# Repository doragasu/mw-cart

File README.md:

# WARNING: THIS PROJECT HAS MOVED

You can find the most recent version at the [mw-cart GitLab project page](https://gitlab.com/doragasu/mw-cart). This repository will be kept as is, and will not be updated anymore.

# mw-cart
MegaWiFi Cartridge

This cartridge is for the MegaWiFi project. It consists of a cartridge for the SEGA Genesis/Megadrive console, along with a WiFi interface, allowing brave programmers to implement games with online gaming, leaderboards, evil DLCs, etc.

This project was initially created for 1985alternativo, but to this day, no brave soul has dared to make an online game using this cart. Will you give it a try?

Have a look to the [github project page](https://github.com/doragasu/mw) for more information.

## License
mw-cart is licensed under the [CERN OHL 1.2](http://www.ohwr.org/licenses/cern-ohl/v1.2) license. You are free to study, distribute and make modifications to the Documentation, under the aforementioned license terms. You are also free to make cartridges derived from the Documentation for non-commercial purposes. If you want to make a commercial Product using this Documentation, please contact me to obtain a licence.

## About CAD files
Electronic CAD design files are for KiCAD Open Source electronics design suite. Please install latest version along with KiCAD libraries to open the project. When opening schematic, KiCAD will most likely complain about missing library "doragasu". Despite this warning, the schematic should load nicely (using the cached libraries). To avoid this message, install [the missing library](https://github.com/doragasu/doragasu-kicad-lib) and make sure to configure it in the schematic editor.

The files under `gerber` directory are for PCB fabrication. Send them to your favorite PCB fab house.

Enjoy!

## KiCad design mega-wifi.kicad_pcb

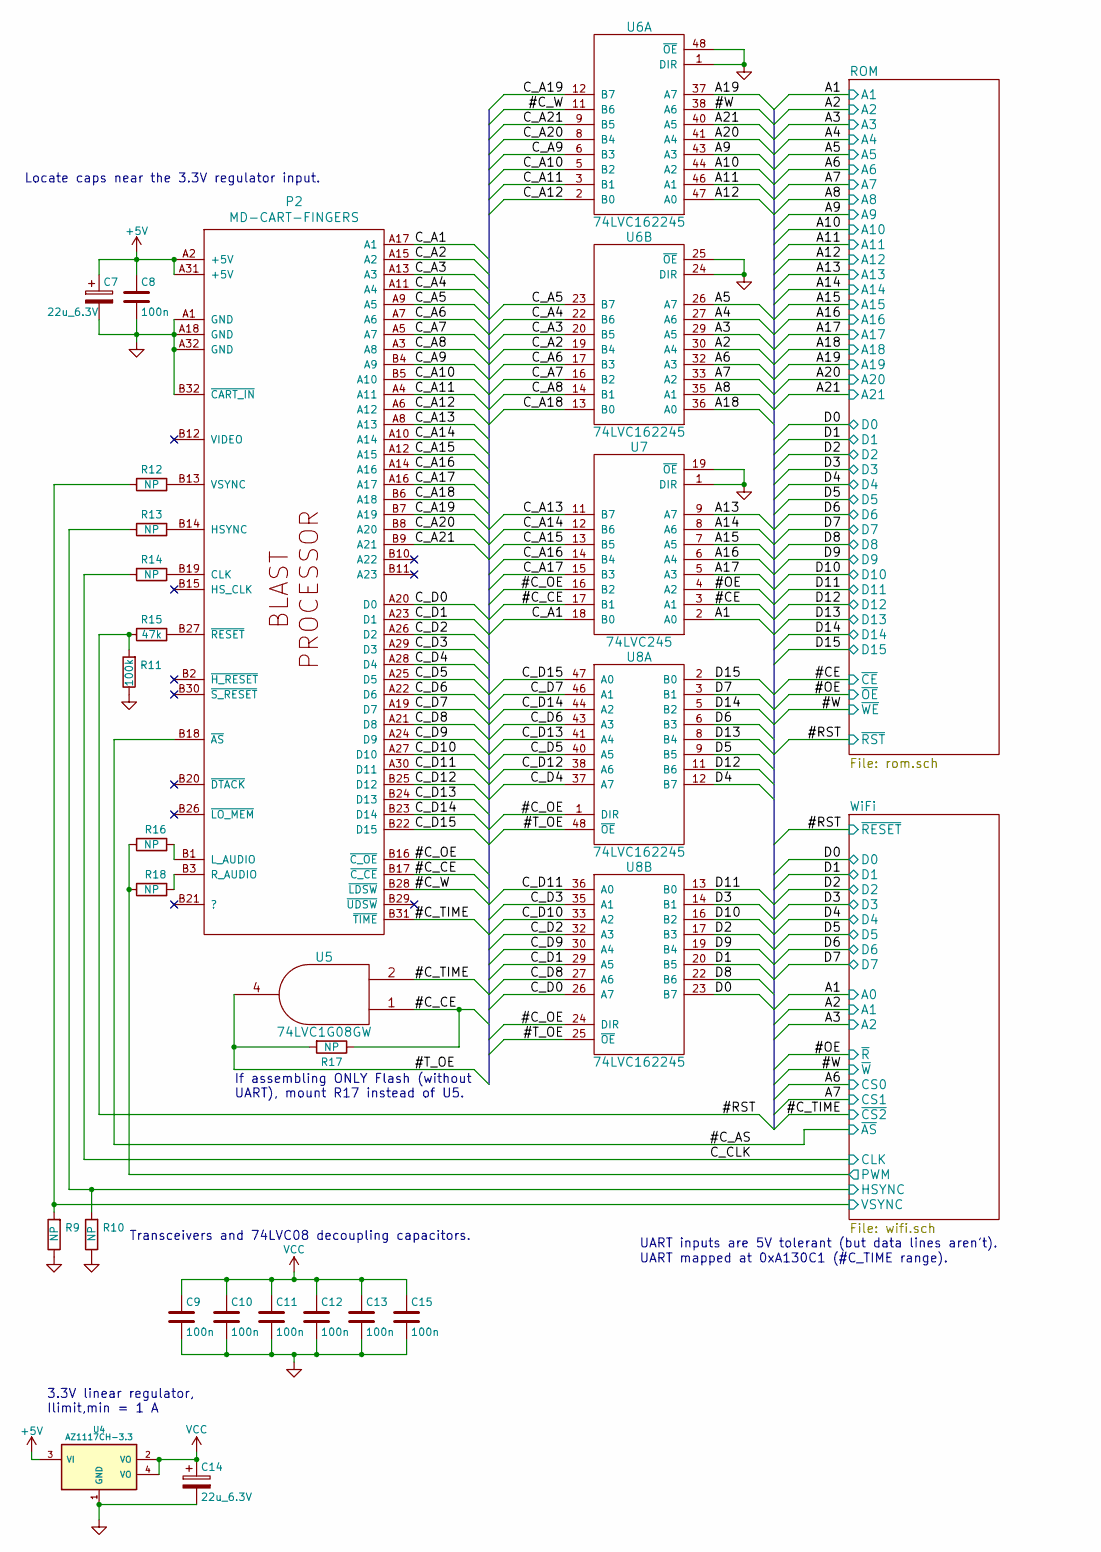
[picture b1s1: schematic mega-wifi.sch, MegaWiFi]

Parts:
C7, C14: 22u_6.3V; c_elec_4x4.5; LCSC# C250865
C8, C9, C10, C11, C12, C13, C15: 100n; C_0805; LCSC# C2830722
P2: MD-CART-FINGERS
R9, R10, R12, R13: NP; R_0805
R11: 100k; R_0805; LCSC# C237121
R14, R16, R17, R18: NP; JUMPER_0805
R15: 47k; R_0805; LCSC# C144558
U4: AZ1117CH-3.3; SOT-223; LCSC# C351784
U5: 74LVC1G08GW; SOT23-5; LCSC# C434068
U6, U8: 74LVC162245; TSSOP-48_6.1x12.5mm_Pitch0.5mm; LCSC# C6069
U7: 74LVC245; SSOP-20_4.4x6.5mm_Pitch0.65mm; LCSC# C393617

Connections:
+5V: C7.1, C8.1, P2.A2 (+5V), P2.A31 (+5V), U4.3 (VI)
/#CE: U7.3 (A1); also elsewhere on the board
/#C_AS: P2.B18 (~AS); also elsewhere on the board
/#C_CE: P2.B17 (~C_CE), R17.1, U5.1 (B), U7.17 (B1)
/#C_OE: P2.B16 (~C_OE), U7.16 (B2), U8.1 (DIR), U8.24 (DIR)
/#C_TIME: P2.B31 (~TIME), U5.2 (A); also elsewhere on the board
/#C_W: P2.B28 (~LDSW), U6.11 (B6)
/#OE: U7.4 (A2); also elsewhere on the board
/#RST: R11.2, R15.1; also elsewhere on the board
/#T_OE: R17.2, U5.4 (Y), U8.25 (~OE), U8.48 (~OE)
/#W: U6.38 (A6); also elsewhere on the board
/A1: U7.2 (A0); also elsewhere on the board
/A2: U6.30 (A4); also elsewhere on the board
/A3: U6.29 (A5); also elsewhere on the board
/A4: U6.27 (A6); also elsewhere on the board
/A5: U6.26 (A7); also elsewhere on the board
/A6: U6.32 (A3); also elsewhere on the board
/A7: U6.33 (A2); also elsewhere on the board
/A8: U6.35 (A1); also elsewhere on the board
/A9: U6.43 (A3); also elsewhere on the board
/A10: U6.44 (A2); also elsewhere on the board
/A11: U6.46 (A1); also elsewhere on the board
/A12: U6.47 (A0); also elsewhere on the board
/A13: U7.9 (A7); also elsewhere on the board
/A14: U7.8 (A6); also elsewhere on the board
/A15: U7.7 (A5); also elsewhere on the board
/A16: U7.6 (A4); also elsewhere on the board
/A17: U7.5 (A3); also elsewhere on the board
/A18: U6.36 (A0); also elsewhere on the board
/A19: U6.37 (A7); also elsewhere on the board
/A20: U6.41 (A4); also elsewhere on the board
/A21: U6.40 (A5); also elsewhere on the board
/C_A1: P2.A17 (A1), U7.18 (B0)
/C_A2: P2.A15 (A2), U6.19 (B4)
/C_A3: P2.A13 (A3), U6.20 (B5)
/C_A4: P2.A11 (A4), U6.22 (B6)
/C_A5: P2.A9 (A5), U6.23 (B7)
/C_A6: P2.A7 (A6), U6.17 (B3)
/C_A7: P2.A5 (A7), U6.16 (B2)
/C_A8: P2.A3 (A8), U6.14 (B1)
/C_A9: P2.B4 (A9), U6.6 (B3)
/C_A10: P2.B5 (A10), U6.5 (B2)
/C_A11: P2.A4 (A11), U6.3 (B1)
/C_A12: P2.A6 (A12), U6.2 (B0)
/C_A13: P2.A8 (A13), U7.11 (B7)
/C_A14: P2.A10 (A14), U7.12 (B6)
/C_A15: P2.A12 (A15), U7.13 (B5)
/C_A16: P2.A14 (A16), U7.14 (B4)
/C_A17: P2.A16 (A17), U7.15 (B3)
/C_A18: P2.B6 (A18), U6.13 (B0)
/C_A19: P2.B7 (A19), U6.12 (B7)
/C_A20: P2.B8 (A20), U6.8 (B4)
/C_A21: P2.B9 (A21), U6.9 (B5)
/C_CLK: R14.2; also elsewhere on the board
/C_D0: P2.A20 (D0), U8.26 (A7)
/C_D1: P2.A23 (D1), U8.29 (A5)
/C_D2: P2.A26 (D2), U8.32 (A3)
/C_D3: P2.A29 (D3), U8.35 (A1)
/C_D4: P2.A28 (D4), U8.37 (A7)
/C_D5: P2.A25 (D5), U8.40 (A5)
/C_D6: P2.A22 (D6), U8.43 (A3)
/C_D7: P2.A19 (D7), U8.46 (A1)
/C_D8: P2.A21 (D8), U8.27 (A6)
/C_D9: P2.A24 (D9), U8.30 (A4)
/C_D10: P2.A27 (D10), U8.33 (A2)
/C_D11: P2.A30 (D11), U8.36 (A0)
/C_D12: P2.B25 (D12), U8.38 (A6)
/C_D13: P2.B24 (D13), U8.41 (A4)
/C_D14: P2.B23 (D14), U8.44 (A2)
/C_D15: P2.B22 (D15), U8.47 (A0)
/D0: U8.23 (B7); also elsewhere on the board
/D1: U8.20 (B5); also elsewhere on the board
/D2: U8.17 (B3); also elsewhere on the board
/D3: U8.14 (B1); also elsewhere on the board
/D4: U8.12 (B7); also elsewhere on the board
/D5: U8.9 (B5); also elsewhere on the board
/D6: U8.6 (B3); also elsewhere on the board
/D7: U8.3 (B1); also elsewhere on the board
/D8: U8.22 (B6); also elsewhere on the board
/D9: U8.19 (B4); also elsewhere on the board
/D10: U8.16 (B2); also elsewhere on the board
/D11: U8.13 (B0); also elsewhere on the board
/D12: U8.11 (B6); also elsewhere on the board
/D13: U8.8 (B4); also elsewhere on the board
/D14: U8.5 (B2); also elsewhere on the board
/D15: U8.2 (B0); also elsewhere on the board
/WiFi/HSYNC: R10.2, R13.1; also elsewhere on the board
/WiFi/PWM: R16.1, R18.1; also elsewhere on the board
/WiFi/VSYNC: R9.2, R12.1; also elsewhere on the board
GND: C7.2, C8.2, C9.2, C10.2, C11.2, C12.2, C13.2, C14.2, C15.2, P2.A1 (GND), P2.A18 (GND), P2.A32 (GND), P2.B32 (~CART_IN), R9.1, R10.1, R11.1, U4.1 (GND), U5.3 (GND), U6.1 (DIR), U6.4 (GND), U6.10 (GND), U6.15 (GND), U6.21 (GND), U6.24 (DIR), U6.25 (~OE), U6.28 (GND), U6.34 (GND), U6.39 (GND), U6.45 (GND), U6.48 (~OE), U7.1 (DIR), U7.10 (GND), U7.19 (~OE), U8.4 (GND), U8.10 (GND), U8.15 (GND), U8.21 (GND), U8.28 (GND), U8.34 (GND), U8.39 (GND), U8.45 (GND); also elsewhere on the board
unnamed: P2.B1 (L_AUDIO), R16.2
unnamed: P2.B3 (R_AUDIO), R18.2
unnamed: P2.B13 (VSYNC), R12.2
unnamed: P2.B14 (HSYNC), R13.2
unnamed: P2.B19 (CLK), R14.1
unnamed: P2.B27 (~RESET), R15.2
VCC: C9.1, C10.1, C11.1, C12.1, C13.1, C14.1, C15.1, U4.2 (VO), U4.4 (VO), U5.5 (VCC), U6.7 (VCC), U6.18 (VCC), U6.31 (VCC), U6.42 (VCC), U7.20 (VCC), U8.7 (VCC), U8.18 (VCC), U8.31 (VCC), U8.42 (VCC); also elsewhere on the board

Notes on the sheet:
UART inputs are 5V tolerant (but data lines aren't).
3.3V linear regulator, Ilimit,min = 1 A
UART mapped at 0xA130C1 (#C_TIME range).
Locate caps near the 3.3V regulator input.
Transceivers and 74LVC08 decoupling capacitors.
If assembling ONLY Flash (without UART), mount R17 instead of U5.

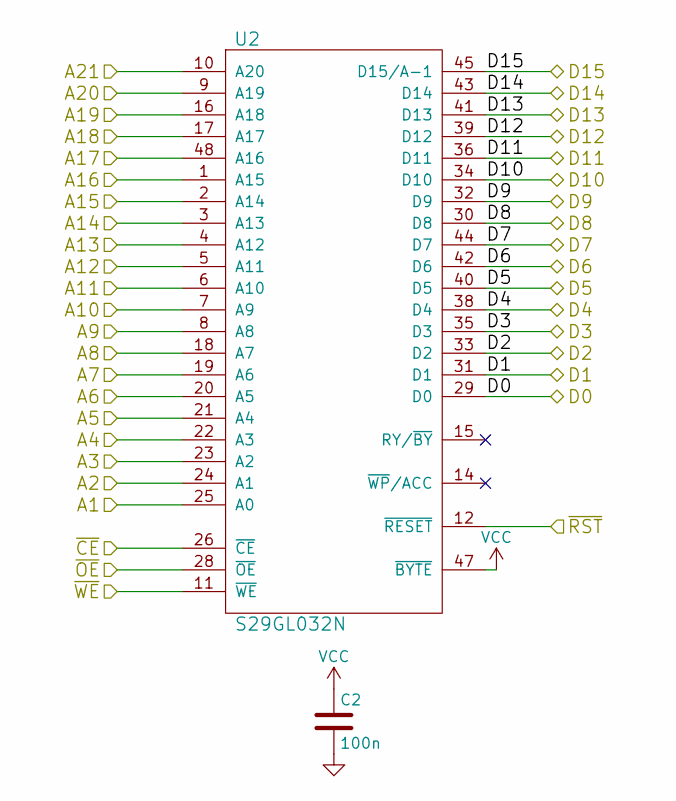
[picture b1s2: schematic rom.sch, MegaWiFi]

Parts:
C2: 100n; C_0805; LCSC# C2830722
U2: S29GL032N; TSOP48SP; LCSC# C62389

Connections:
/#CE: U2.26 (~CE); also elsewhere on the board
/#OE: U2.28 (~OE); also elsewhere on the board
/#RST: U2.12 (~RESET); also elsewhere on the board
/#W: U2.11 (~WE); also elsewhere on the board
/A1: U2.25 (A0); also elsewhere on the board
/A2: U2.24 (A1); also elsewhere on the board
/A3: U2.23 (A2); also elsewhere on the board
/A4: U2.22 (A3); also elsewhere on the board
/A5: U2.21 (A4); also elsewhere on the board
/A6: U2.20 (A5); also elsewhere on the board
/A7: U2.19 (A6); also elsewhere on the board
/A8: U2.18 (A7); also elsewhere on the board
/A9: U2.8 (A8); also elsewhere on the board
/A10: U2.7 (A9); also elsewhere on the board
/A11: U2.6 (A10); also elsewhere on the board
/A12: U2.5 (A11); also elsewhere on the board
/A13: U2.4 (A12); also elsewhere on the board
/A14: U2.3 (A13); also elsewhere on the board
/A15: U2.2 (A14); also elsewhere on the board
/A16: U2.1 (A15); also elsewhere on the board
/A17: U2.48 (A16); also elsewhere on the board
/A18: U2.17 (A17); also elsewhere on the board
/A19: U2.16 (A18); also elsewhere on the board
/A20: U2.9 (A19); also elsewhere on the board
/A21: U2.10 (A20); also elsewhere on the board
/D0: U2.29 (D0); also elsewhere on the board
/D1: U2.31 (D1); also elsewhere on the board
/D2: U2.33 (D2); also elsewhere on the board
/D3: U2.35 (D3); also elsewhere on the board
/D4: U2.38 (D4); also elsewhere on the board
/D5: U2.40 (D5); also elsewhere on the board
/D6: U2.42 (D6); also elsewhere on the board
/D7: U2.44 (D7); also elsewhere on the board
/D8: U2.30 (D8); also elsewhere on the board
/D9: U2.32 (D9); also elsewhere on the board
/D10: U2.34 (D10); also elsewhere on the board
/D11: U2.36 (D11); also elsewhere on the board
/D12: U2.39 (D12); also elsewhere on the board
/D13: U2.41 (D13); also elsewhere on the board
/D14: U2.43 (D14); also elsewhere on the board
/D15: U2.45 (D15/A-1); also elsewhere on the board
GND: C2.2, U2.27 (GND), U2.46 (GND); also elsewhere on the board
VCC: C2.1, U2.37 (VCC), U2.47 (~BYTE); also elsewhere on the board

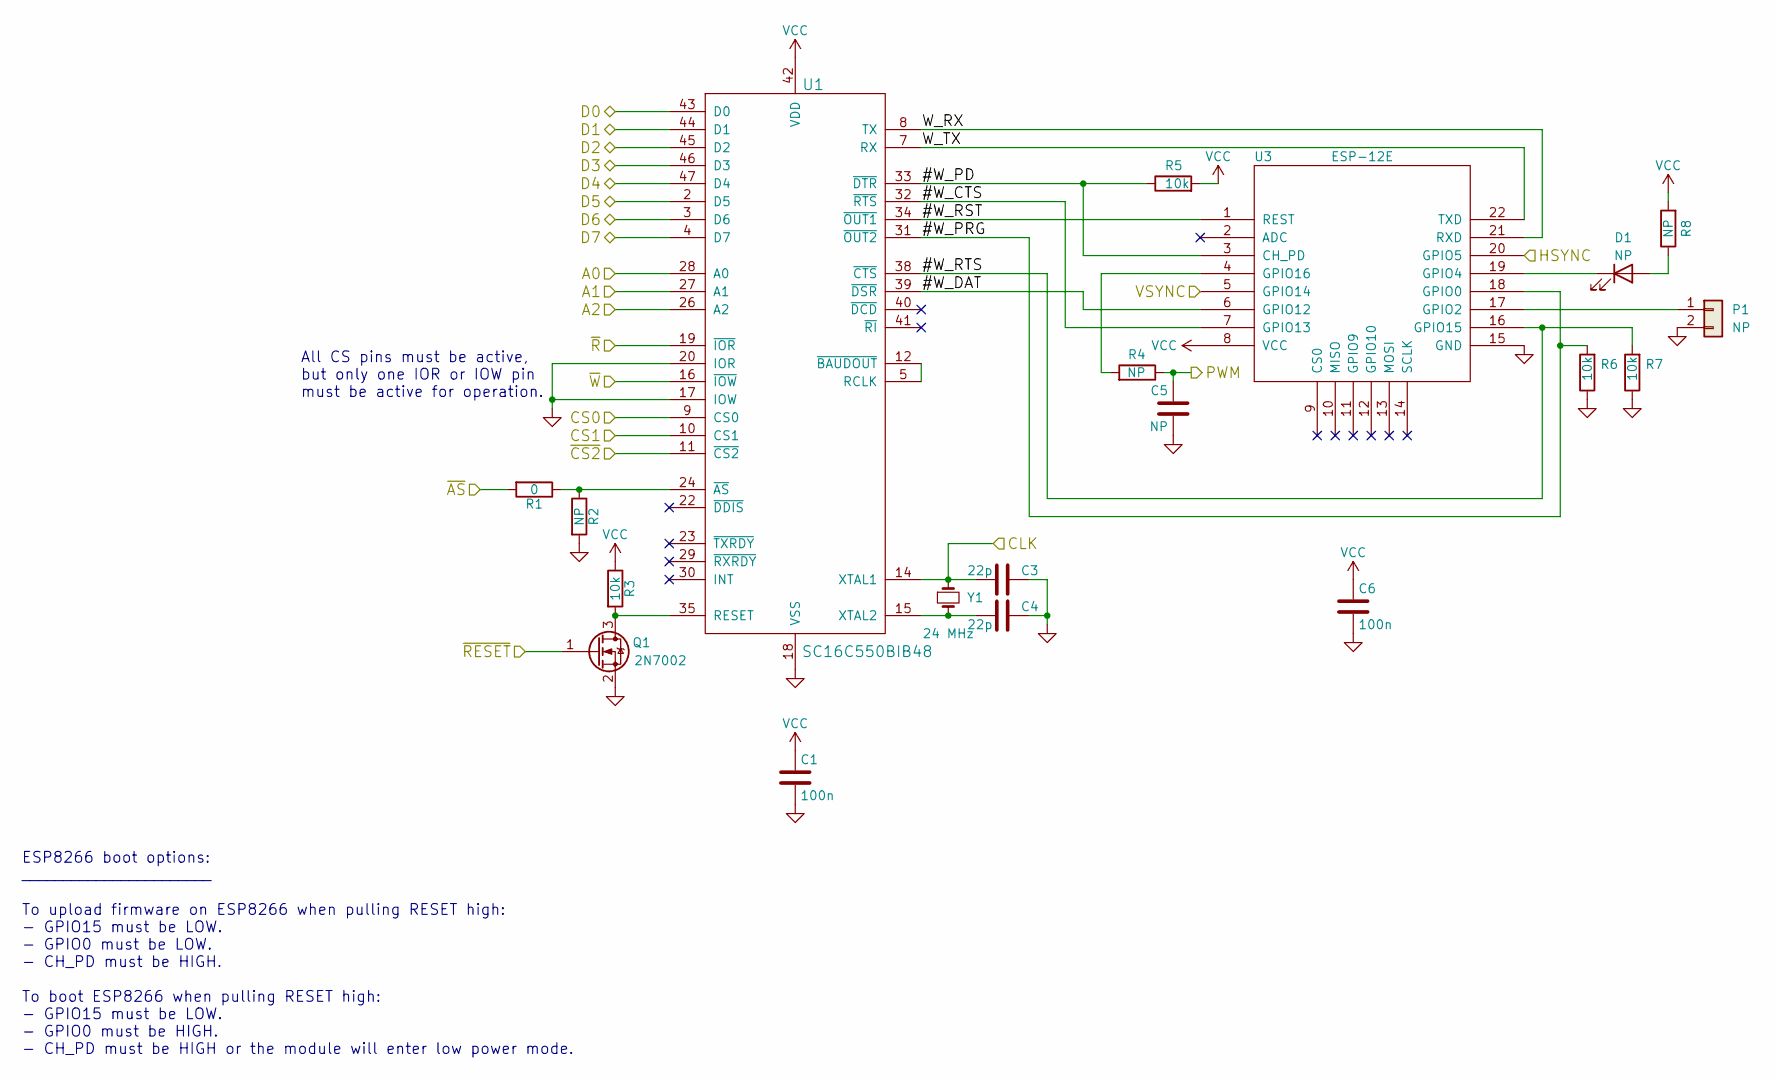
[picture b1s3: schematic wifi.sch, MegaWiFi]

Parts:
C1, C6: 100n; C_0805; LCSC# C2830722
C3, C4: 22p; C_0805; LCSC# C237185
C5: NP; C_0805; LCSC# C2830722
D1: NP; LED-0603
P1: NP; PinHeader_1x02_P2.54mm_Vertical
Q1: 2N7002; sot23; LCSC# C306856
R1: 0; JUMPER_0805; LCSC# C96345
R2, R4, R8: NP; R_0805
R3, R5, R6, R7: 10k; R_0805; LCSC# C2763777
U1: SC16C550BIB48; TQFP-48_7x7mm_Pitch0.5mm; LCSC# C84320
U3: ESP-12E; LCSC# C89297
Y1: 24 MHz; Crystal_HC49-SD_SMD; LCSC# C259050

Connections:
/#C_AS: R1.2; also elsewhere on the board
/#C_TIME: U1.11 (~CS2); also elsewhere on the board
/#OE: U1.19 (~IOR); also elsewhere on the board
/#RST: Q1.1 (G); also elsewhere on the board
/#W: U1.16 (~IOW); also elsewhere on the board
/A1: U1.28 (A0); also elsewhere on the board
/A2: U1.27 (A1); also elsewhere on the board
/A3: U1.26 (A2); also elsewhere on the board
/A6: U1.9 (CS0); also elsewhere on the board
/A7: U1.10 (CS1); also elsewhere on the board
/C_CLK: C3.2, U1.14 (XTAL1), Y1.1; also elsewhere on the board
/D0: U1.43 (D0); also elsewhere on the board
/D1: U1.44 (D1); also elsewhere on the board
/D2: U1.45 (D2); also elsewhere on the board
/D3: U1.46 (D3); also elsewhere on the board
/D4: U1.47 (D4); also elsewhere on the board
/D5: U1.2 (D5); also elsewhere on the board
/D6: U1.3 (D6); also elsewhere on the board
/D7: U1.4 (D7); also elsewhere on the board
/WiFi/#W_CTS: U1.32 (~RTS), U3.7 (GPIO13)
/WiFi/#W_DAT: U1.39 (~DSR), U3.6 (GPIO12)
/WiFi/#W_PD: R5.1, U1.33 (~DTR), U3.3 (CH_PD)
/WiFi/#W_PRG: R6.2, U1.31 (~OUT2), U3.18 (GPIO0)
/WiFi/#W_RST: U1.34 (~OUT1), U3.1 (REST)
/WiFi/#W_RTS: R7.2, U1.38 (~CTS), U3.16 (GPIO15)
/WiFi/HSYNC: U3.20 (GPIO5); also elsewhere on the board
/WiFi/PWM: C5.1, R4.1; also elsewhere on the board
/WiFi/VSYNC: U3.5 (GPIO14); also elsewhere on the board
/WiFi/W_RX: U1.8 (TX), U3.21 (RXD)
/WiFi/W_TX: U1.7 (RX), U3.22 (TXD)
GND: C1.2, C3.1, C4.1, C5.2, C6.2, P1.2, Q1.2 (S), R2.2, R6.1, R7.1, U1.17 (IOW), U1.18 (VSS), U1.20 (IOR), U3.15 (GND); also elsewhere on the board
unnamed: C4.2, U1.15 (XTAL2), Y1.2
unnamed: D1.1 (K), U3.19 (GPIO4)
unnamed: D1.2 (A), R8.1
unnamed: P1.1, U3.17 (GPIO2)
unnamed: Q1.3 (D), R3.2, U1.35 (RESET)
unnamed: R1.1, R2.1, U1.24 (~AS)
unnamed: R4.2, U3.4 (GPIO16)
unnamed: U1.5 (RCLK), U1.12 (~BAUDOUT)
VCC: C1.1, C6.1, R3.1, R5.2, R8.2, U1.42 (VDD), U3.8 (VCC); also elsewhere on the board

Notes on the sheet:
ESP8266 boot options: _______________________ To upload firmware on ESP8266 when pulling RESET high: - GPIO15 must be LOW. - GPIO0 must be LOW. - CH_PD must be HIGH. To boot ESP8266 when pulling RESET high: - GPIO15 must be LOW. - GPIO0 must be HIGH. - CH_PD must be HIGH or the module will enter lo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
All CS pins must be active, but only one IOR or IOW pin must be active for operation.

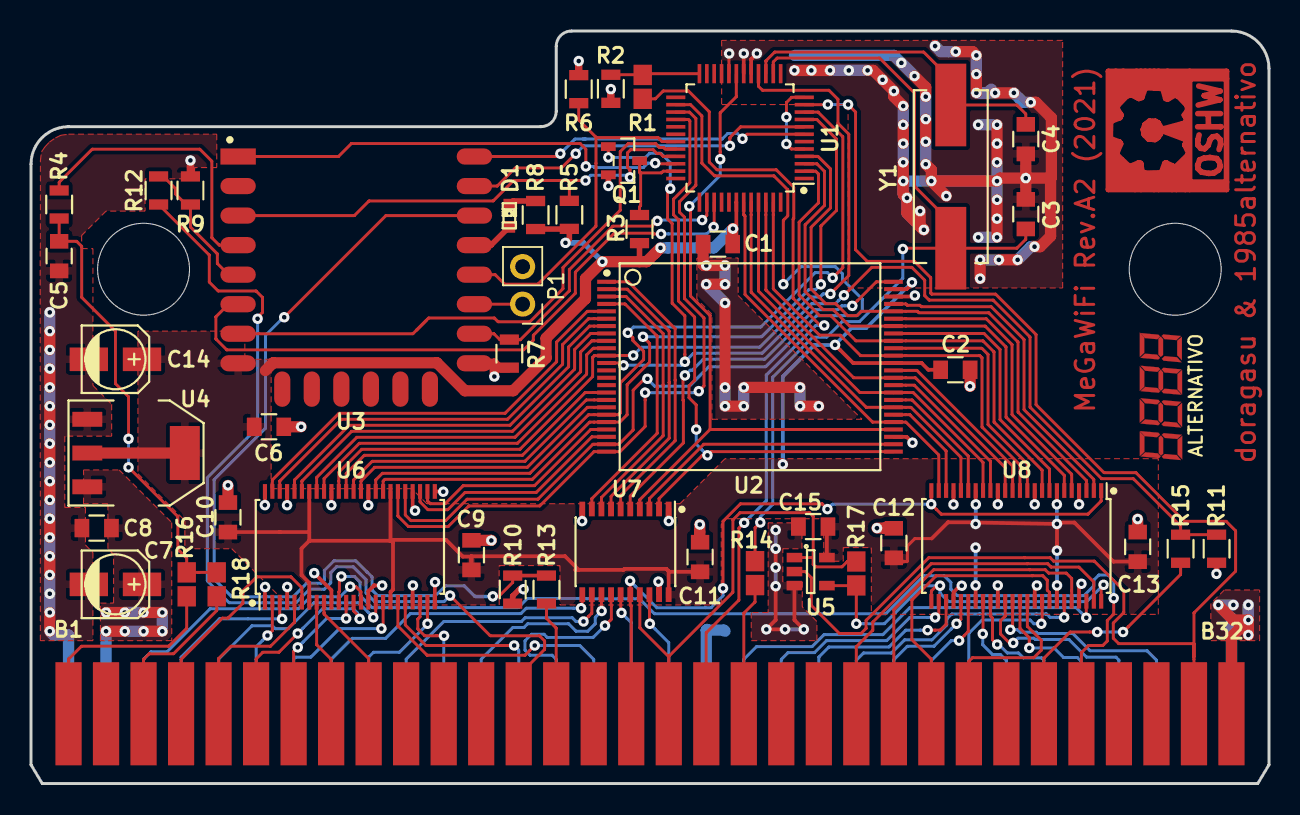
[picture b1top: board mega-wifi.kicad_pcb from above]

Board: 2 copper layers, 83.8 x 51.0 mm, 47 parts (0 on the bottom side), 113 nets.

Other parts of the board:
Symbol_OSHW-Logo_CopperTop_Negative: VAL**; Symbol_OSHW-Logo_CopperTop_Negative

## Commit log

2017-03-24 Added design files.
2018-04-07 Updated to latest KiCad and libraries version.
2021-10-30 Update schematic components to latest library
2021-10-30 Update 3D models to latest library

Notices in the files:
mega-wifi.kicad_pcb:
License: TBD
mega-wifi.sch:
License: CERN OHL 1.2
